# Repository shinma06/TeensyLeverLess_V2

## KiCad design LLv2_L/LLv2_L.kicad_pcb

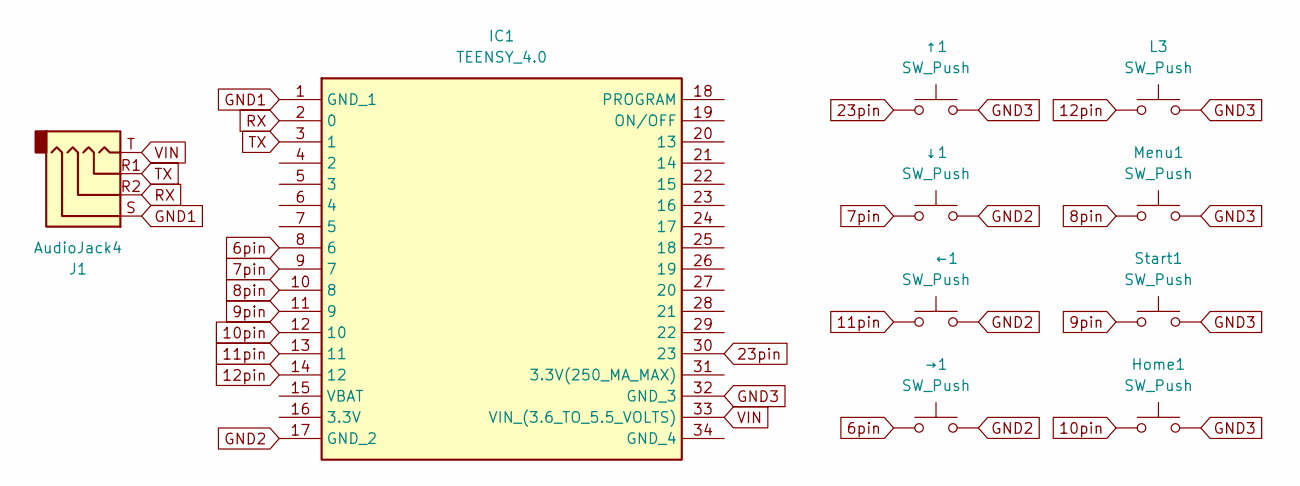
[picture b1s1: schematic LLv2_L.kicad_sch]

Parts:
Home1: SW_Push; SW_PUSH_6mm_H4.3mm
IC1: TEENSY_4.0; Teensy 4.0 LL; Manufacturer_Part_Number TEENSY 4.0
J1: AudioJack4; TRRS LL
L3: SW_Push; SW_Kailh_Choc_V2_Lofree_Flow
Menu1: SW_Push; SW_PUSH_6mm_H4.3mm
Start1: SW_Push; SW_PUSH_6mm_H4.3mm
←1: SW_Push; SW_Kailh_Choc_V2_Lofree_Flow
↑1: SW_Push; SW_Kailh_Choc_V2_Lofree_Flow
→1: SW_Push; SW_Kailh_Choc_V2_Lofree_Flow
↓1: SW_Push; SW_Kailh_Choc_V2_Lofree_Flow

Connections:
6pin: IC1.8 (6), →1.1
7pin: IC1.9 (7), ↓1.1
8pin: IC1.10 (8), Menu1.2
9pin: IC1.11 (9), Start1.2
10pin: Home1.2, IC1.12 (10)
11pin: IC1.13 (11), ←1.1
12pin: IC1.14 (12), L3.1
23pin: IC1.30 (23), ↑1.1
GND1: IC1.1 (GND_1), J1.S
GND2: IC1.17 (GND_2), ←1.2, →1.2, ↓1.2
GND3: Home1.1, IC1.32 (GND_3), L3.2, Menu1.1, Start1.1, ↑1.2
RX: IC1.2 (0), J1.R2
TX: IC1.3 (1), J1.R1
VIN: IC1.33 (VIN_(3.6_TO_5.5_VOLTS)), J1.T

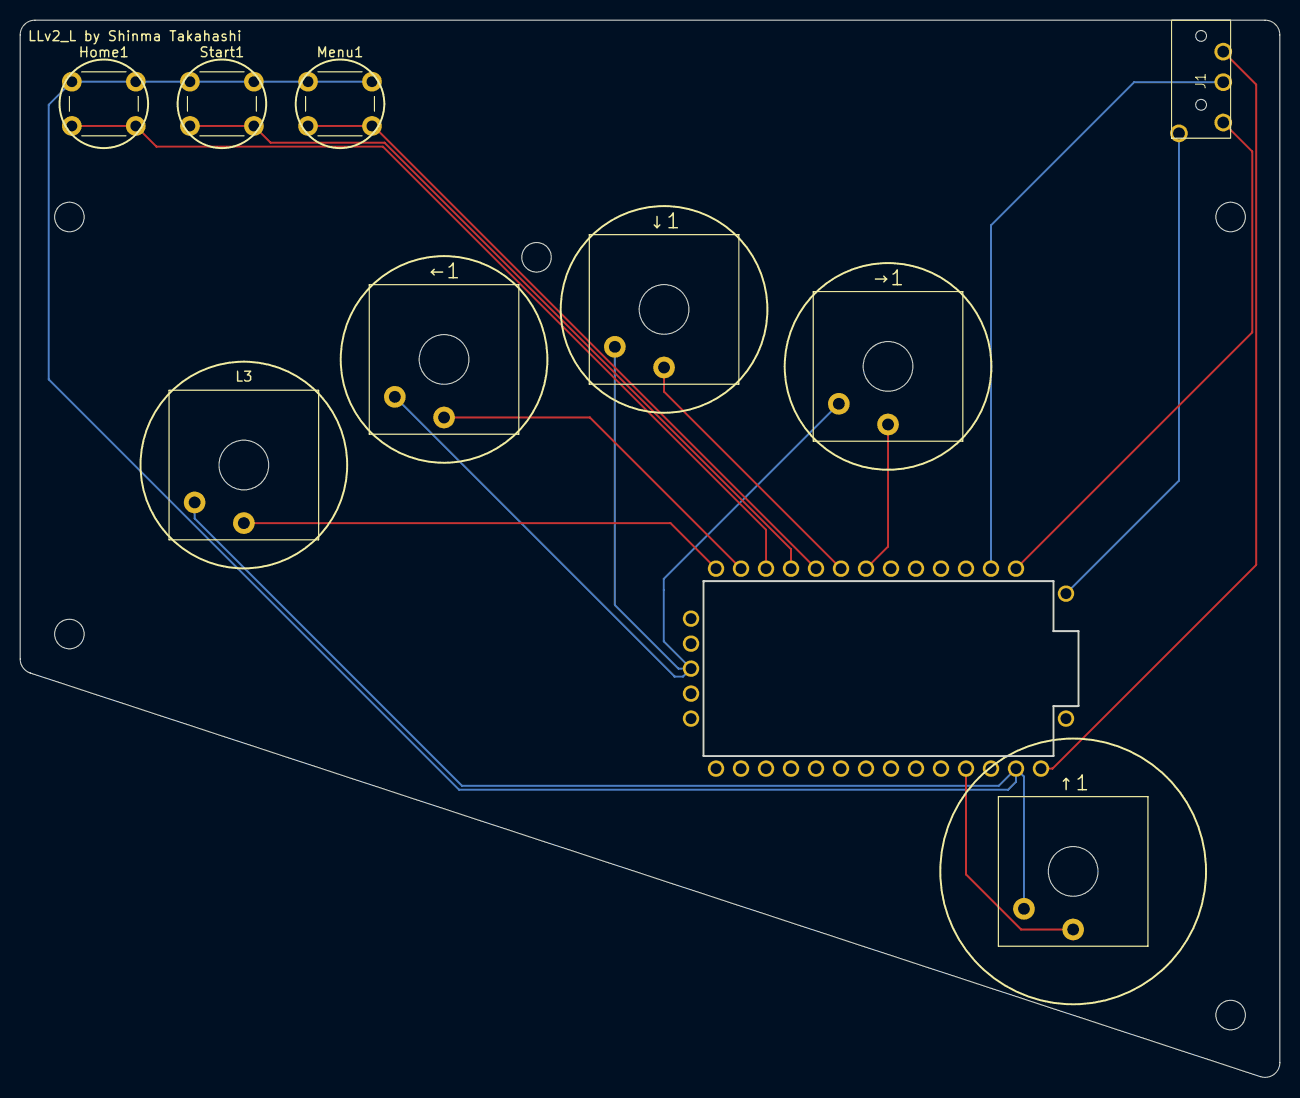
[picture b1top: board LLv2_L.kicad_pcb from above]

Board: 2 copper layers, 128.0 x 107.4 mm, 10 parts (0 on the bottom side), 14 nets.

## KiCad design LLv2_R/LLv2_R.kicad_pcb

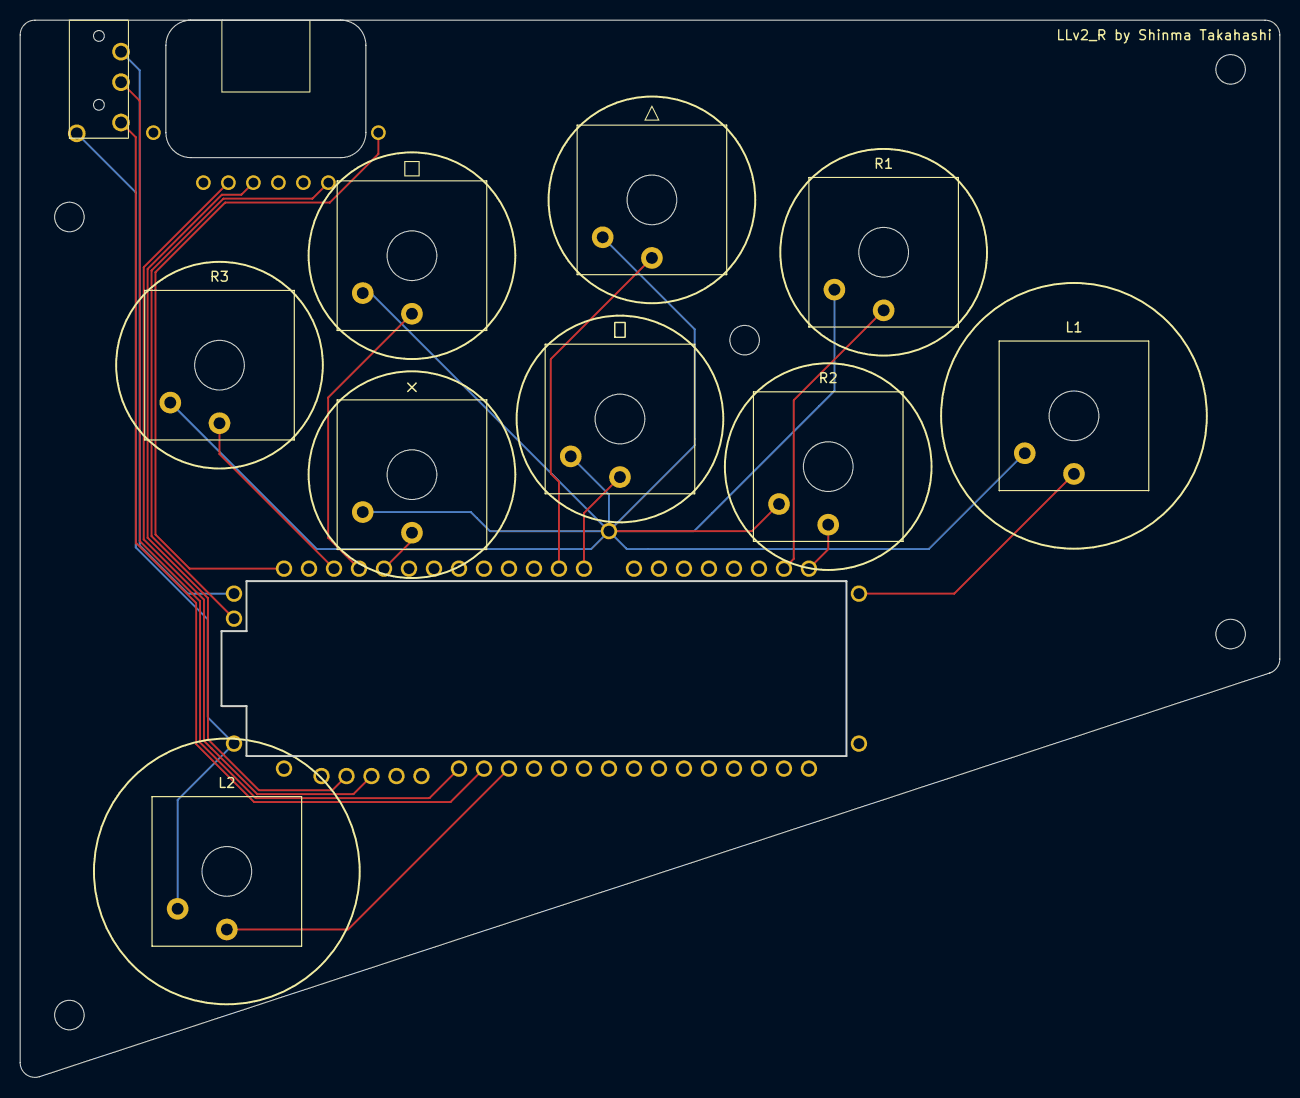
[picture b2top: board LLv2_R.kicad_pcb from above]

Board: 2 copper layers, 128.0 x 107.4 mm, 12 parts (0 on the bottom side), 18 nets.

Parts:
4090USBCBreakout1: 4090 LL
J1: AudioJack4; TRRS LL
L1, L2: SW_Push; SW_Kailh_Choc_V2_Lofree_Flow
R1, R2, R3: SW_Push; SW_Kailh_Choc_V2_Lofree_Flow
Teensy4.1: Teensy 4.1 LL
×: SW_Push; SW_Kailh_Choc_V2_Lofree_Flow
□: SW_Push; SW_Kailh_Choc_V2_Lofree_Flow
△: SW_Push; SW_Kailh_Choc_V2_Lofree_Flow
〇: SW_Push; SW_Kailh_Choc_V2_Lofree_Flow

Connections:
unnamed: 4090USBCBreakout1.3 (D+), Teensy4.1.50 (D+)
unnamed: 4090USBCBreakout1.4 (D-), Teensy4.1.51 (D-)
unnamed: 4090USBCBreakout1.8 (GND), Teensy4.1.70 (GND_5)
unnamed: 4090USBCBreakout1.7 (VBUS), Teensy4.1.68 (VUSB)
unnamed: Teensy4.1.14 (A0), △.1
unnamed: Teensy4.1.21 (A7), ×.1
unnamed: Teensy4.1.22 (A8), □.1
unnamed: R3.1, Teensy4.1.23 (A9)
unnamed: L1.2, R1.2, R2.2, R3.2, Teensy4.1.69 (GND_4), ×.2, □.2, △.2, 〇.2
unnamed: J1.S, L2.2, Teensy4.1.71 (GND_6)
unnamed: L1.1, Teensy4.1.33 (MCLK2)
unnamed: L2.1, Teensy4.1.9 (OUT1C)
unnamed: J1.R1, Teensy4.1.7 (RX2)
unnamed: R2.1, Teensy4.1.34 (RX8)
unnamed: Teensy4.1.13 (SCK), 〇.1
unnamed: J1.R2, Teensy4.1.8 (TX2)
unnamed: R1.1, Teensy4.1.35 (TX8)
unnamed: J1.T, Teensy4.1.55 (VIN_(3.6_TO_5.5_VOLTS))

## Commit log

2024-05-30 firstcommit
2024-05-30 Add KiCad_LLv2plugins as a submodule
2024-05-30 Add 3DModels
2024-05-30 Rename 3DModels
2024-05-30 Update 3DModels
2024-05-31 Update Softwere
2024-06-01 add testerfile
2024-06-02 add test script
